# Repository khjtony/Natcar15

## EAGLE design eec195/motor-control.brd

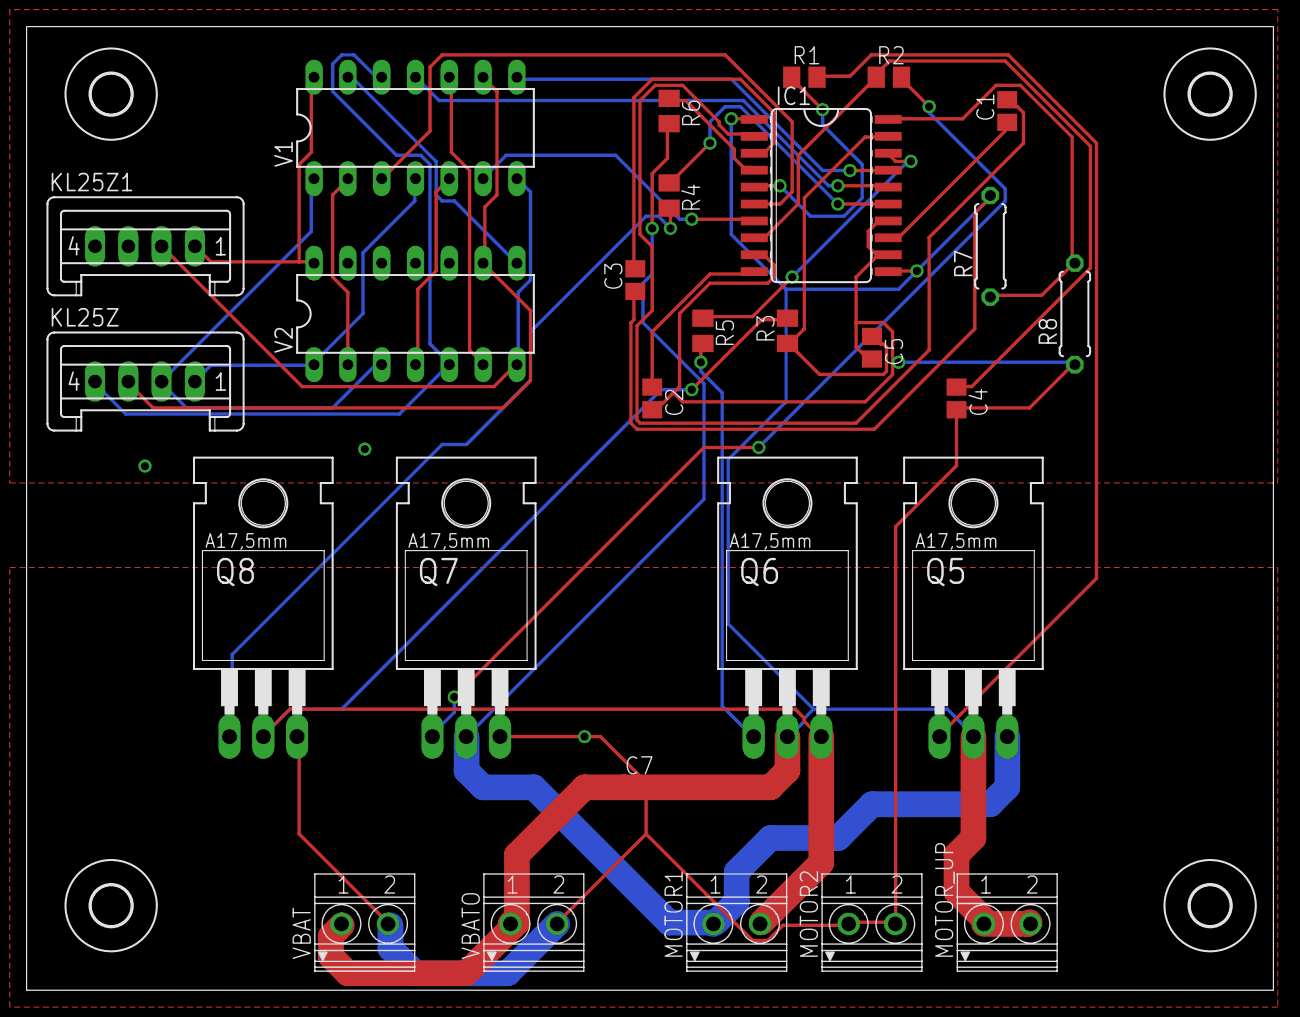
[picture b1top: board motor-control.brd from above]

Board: 2 copper layers, 93.7 x 72.4 mm, 32 parts (0 on the bottom side), 33 nets.

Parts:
C1: 33 nF; C0805
C2, C3: 470 nF; C0805
C4, C5: 10 nF; C0805
C7: 1000 uF; C0805
H1, H2, H3, H4: MOUNT-HOLE3.0; 3,0
IC1: MC33883DW; SO20L
KL25Z, KL25Z1: S04P
MOTOR1, MOTOR2: 1751248
MOTOR_UP: 1751248
Q5, Q6, Q7, Q8: IRF3704; TO220AH
R1, R2, R4, R5: 50; M0805
R3, R6: 10; M0805
R7, R8: 0207/7
V1: 7408N; DIL14
V2: 7404N; DIL14
VBAT: 1751248
VBATO: 1751248

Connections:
GND: C2.2, C4.2, C5.2, C7.2, IC1.9, IC1.12, IC1.14, MOTOR2.1, MOTOR2.2, Q7.E, Q8.E, R8.1, VBAT.2, VBATO.2
unnamed: IC1.17, V1.8
unnamed: V1.2, V2.2
unnamed: IC1.6, V1.3
unnamed: IC1.7, V1.6
unnamed: C1.1, IC1.13
unnamed: C1.2, IC1.2
unnamed: KL25Z1.1, V1.14, V2.14
unnamed: C2.1, IC1.10
unnamed: C3.2, IC1.3
unnamed: IC1.5, R1.1
unnamed: Q5.B, R1.2
unnamed: MOTOR1.2, Q6.E, Q8.C, R3.2
unnamed: KL25Z1.2, V1.7, V2.7
unnamed: C3.1, C7.1, IC1.1, IC1.11, MOTOR_UP.1, MOTOR_UP.2, Q5.C, Q6.C, R7.2, VBAT.1, VBATO.1
unnamed: MOTOR1.1, Q5.E, Q7.C, R6.2
unnamed: Q6.B, R5.2
unnamed: Q8.B, R4.2
unnamed: C5.1, IC1.19, R3.1
unnamed: IC1.4, R6.1
unnamed: C4.1, IC1.8, R2.1
unnamed: KL25Z.2, V1.1, V2.3
unnamed: IC1.20, R7.1, R8.2
unnamed: V1.5, V2.4
unnamed: KL25Z.1, V1.4, V2.1
unnamed: V1.10, V2.6
unnamed: V1.13, V2.8
unnamed: KL25Z.4, V1.12, V2.5
unnamed: IC1.16, V1.11
unnamed: KL25Z.3, V1.9, V2.9
unnamed: Q7.B, R2.2
unnamed: IC1.18, R5.1
unnamed: IC1.15, R4.1

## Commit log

2014-11-26 Create new repo
2014-11-30 Create new program structure by change new global variable
2014-12-02 separate all crucial functions
2014-12-03 debug for camera analysis
2014-12-05 Lab7 Part 3 finished
2014-12-05 lab 7 part 2 finishied Also this version combines all the parts together
2015-01-07 now is Winter 2015 LOL
2015-01-15 some modification
2015-01-20 I ....hate this thing
2015-01-28 daily commit
2015-02-20 custom motor driver
2015-03-01 worked 1.0
2015-03-01 with accel
2015-03-01 can use
2015-03-02 high speed
2015-03-02 high speed 1.1
2015-03-02 23s high speed 1.2
2015-03-02 24s done
2015-03-05 new age
2015-03-08 finish speed feedback and accel
2015-03-09 speed feedback issue
2015-03-09 feedback issue
2015-03-09 tpm repaired
2015-03-09 cross camera
2015-03-09 new start
2015-03-09 mile stone
2015-03-09 not work
2015-03-09 22.49
